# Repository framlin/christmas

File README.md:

# christmas
christmas-window-illumination

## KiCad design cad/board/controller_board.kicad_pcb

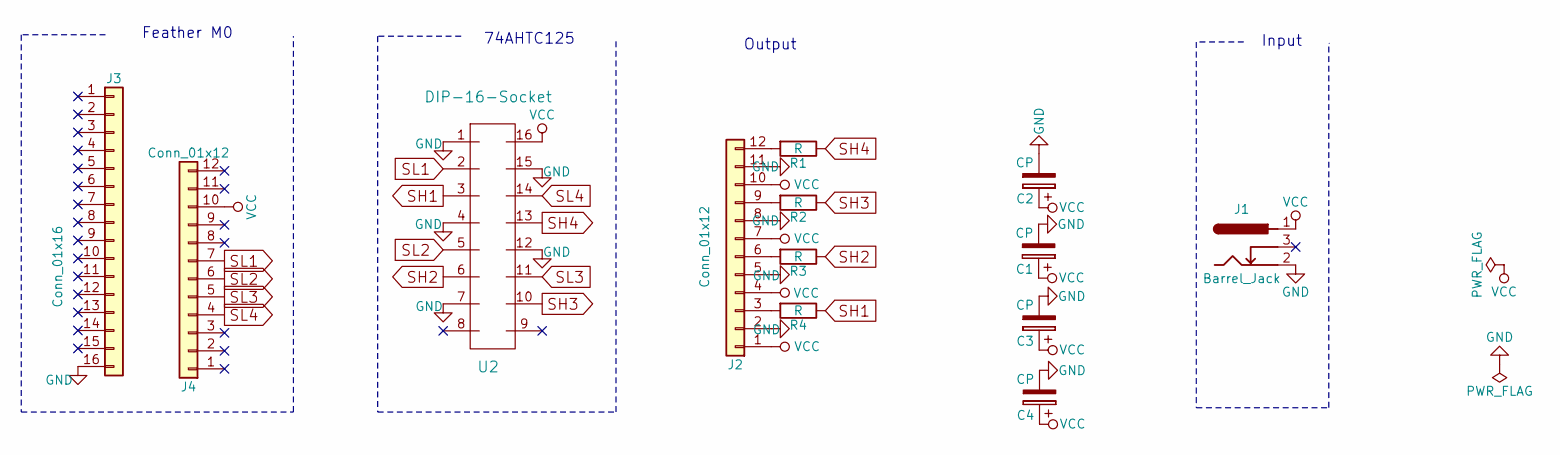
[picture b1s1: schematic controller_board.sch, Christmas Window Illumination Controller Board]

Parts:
C1, C2, C3, C4: CP; CP_Radial_D10.0mm_P5.00mm
J1: Barrel_Jack; Barrel_Jack_CUI_PJ-102AH
J2, J4: Conn_01x12; Pin_Header_Straight_1x12_Pitch2.54mm
J3: Conn_01x16; Pin_Header_Straight_1x16_Pitch2.54mm
R1, R2, R3, R4: R; R_Axial_DIN0207_L6.3mm_D2.5mm_P15.24mm_Horizontal
U2: DIP-16-Socket; DIP-16_W7.62mm

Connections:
GND: C1.2, C2.2, C3.2, C4.2, J1.2, J2.2, J2.5, J2.8, J2.11, J3.16, U2.1, U2.4, U2.7, U2.12, U2.15
unnamed: J2.3, R4.2
unnamed: J2.6, R3.2
unnamed: J2.9, R2.2
unnamed: J2.12, R1.2
SH1: R4.1, U2.3
SH2: R3.1, U2.6
SH3: R2.1, U2.10
SH4: R1.1, U2.13
SL1: J4.7, U2.2
SL2: J4.6, U2.5
SL3: J4.5, U2.11
SL4: J4.4, U2.14
VCC: C1.1, C2.1, C3.1, C4.1, J1.1, J2.1, J2.4, J2.7, J2.10, J4.10, U2.16

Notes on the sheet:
Feather M0
74AHTC125
Output
Input

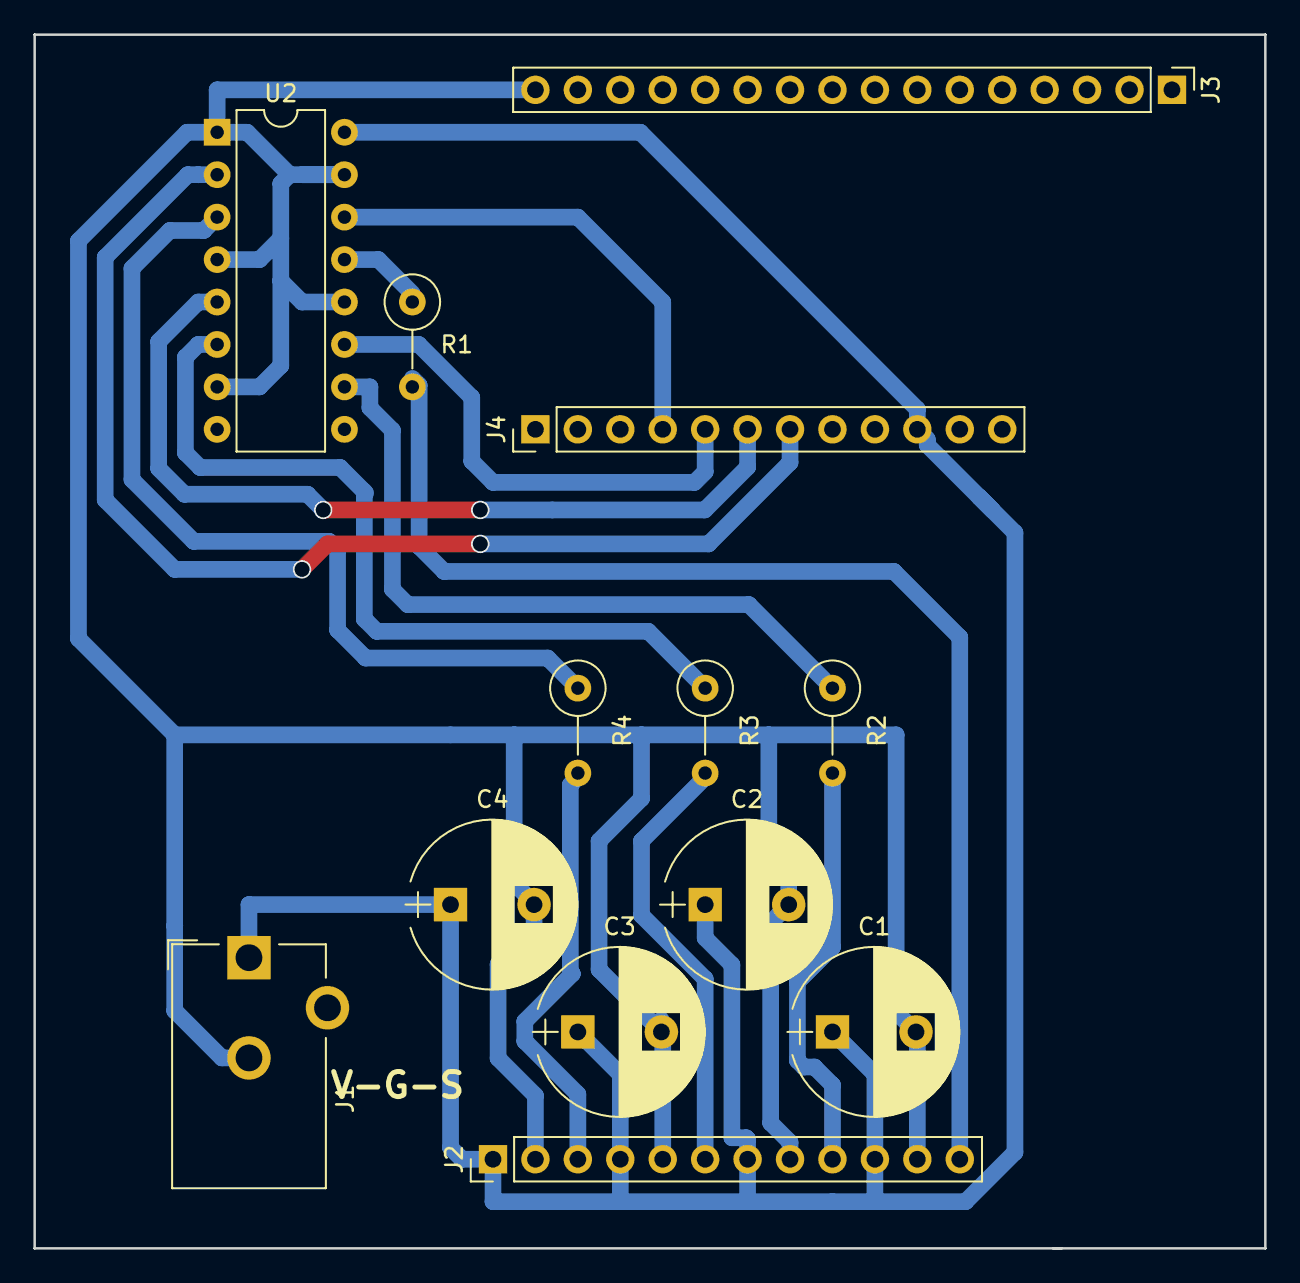
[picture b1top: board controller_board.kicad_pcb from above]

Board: 2 copper layers, 73.7 x 72.6 mm, 13 parts (0 on the bottom side), 14 nets.

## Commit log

2017-11-24 first rough version
2017-11-25 better layout, gcode
2017-11-25 move up-left
2017-11-26 drill missing holes
2017-11-28 drill power
2017-11-30 re-design board with wider tracks, remove all unused copper with cam
2017-12-01 dunno
2017-12-01 clean old gc-files, use 2mm for milling bit
2017-12-02 fix cutout
2018-04-29 dont know
